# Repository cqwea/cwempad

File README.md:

This was a project i did late at night because i didnt sleep and started to design pcb's turned out it was really fun than i finished it all up there

 Bill Of Material
| Item | Quantity | Link |
| --- | --- | --- |
| Seeed XIAO RP2040 | 1 | [Link](https://www.seeedstudio.com/XIAO-RP2040-v1-0-p-5026.html) |
| MX Switches | 4 | [Link](https://www.amazon.com) |
| Keycaps | 4 | [Link](https://www.amazon.com) |
| Oled l2c 0.91inch screen | 1  | [Link](https://www.amazon.com) |
| Rotary encoder switch | 1 | [Link](https://www.amazon.com) |
| 3D Printed Case | 1 | Custom |
| Custom Pcb | 1 | Pcbway.com |

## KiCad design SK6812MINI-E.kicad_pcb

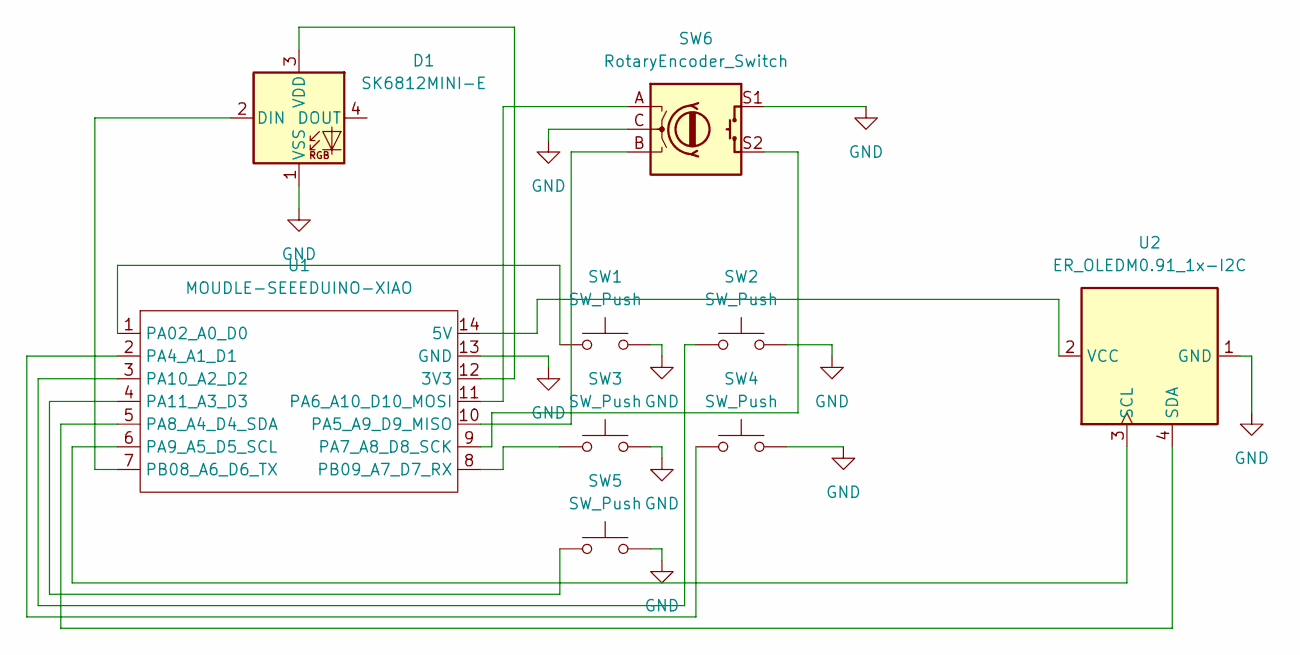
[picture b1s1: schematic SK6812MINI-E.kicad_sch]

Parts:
D1: SK6812MINI-E; LED_SK6812MINI-E_3.2x2.8mm_P1.5mm_ReverseMount
SW1, SW2, SW3, SW4, SW5: SW_Push; SW_Cherry_MX_1.00u_PCB
SW6: RotaryEncoder_Switch; RotaryEncoder_Alps_EC11E-Switch_Vertical_H20mm
U1: MOUDLE-SEEEDUINO-XIAO; XIAO-Generic-Hybrid-14P-2.54-21X17.8MM
U2: ER_OLEDM0.91_1x-I2C

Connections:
GND: D1.1 (VSS), SW1.2, SW2.2, SW3.2, SW4.2, SW5.2, SW6.C, SW6.S1, U1.13 (GND), U2.1 (GND)
unnamed: D1.2 (DIN), U1.7 (PB08_A6_D6_TX)
unnamed: D1.3 (VDD), U1.12 (3V3)
unnamed: U1.14 (5V), U2.2 (VCC)
unnamed: SW1.1, U1.1 (PA02_A0_D0)
unnamed: SW4.1, U1.2 (PA4_A1_D1)
unnamed: SW6.B, U1.10 (PA5_A9_D9_MISO)
unnamed: SW6.A, U1.11 (PA6_A10_D10_MOSI)
unnamed: SW6.S2, U1.9 (PA7_A8_D8_SCK)
unnamed: U1.5 (PA8_A4_D4_SDA), U2.4 (SDA)
unnamed: U1.6 (PA9_A5_D5_SCL), U2.3 (SCL)
unnamed: SW2.1, U1.3 (PA10_A2_D2)
unnamed: SW5.1, U1.4 (PA11_A3_D3)
unnamed: SW3.1, U1.8 (PB09_A7_D7_RX)

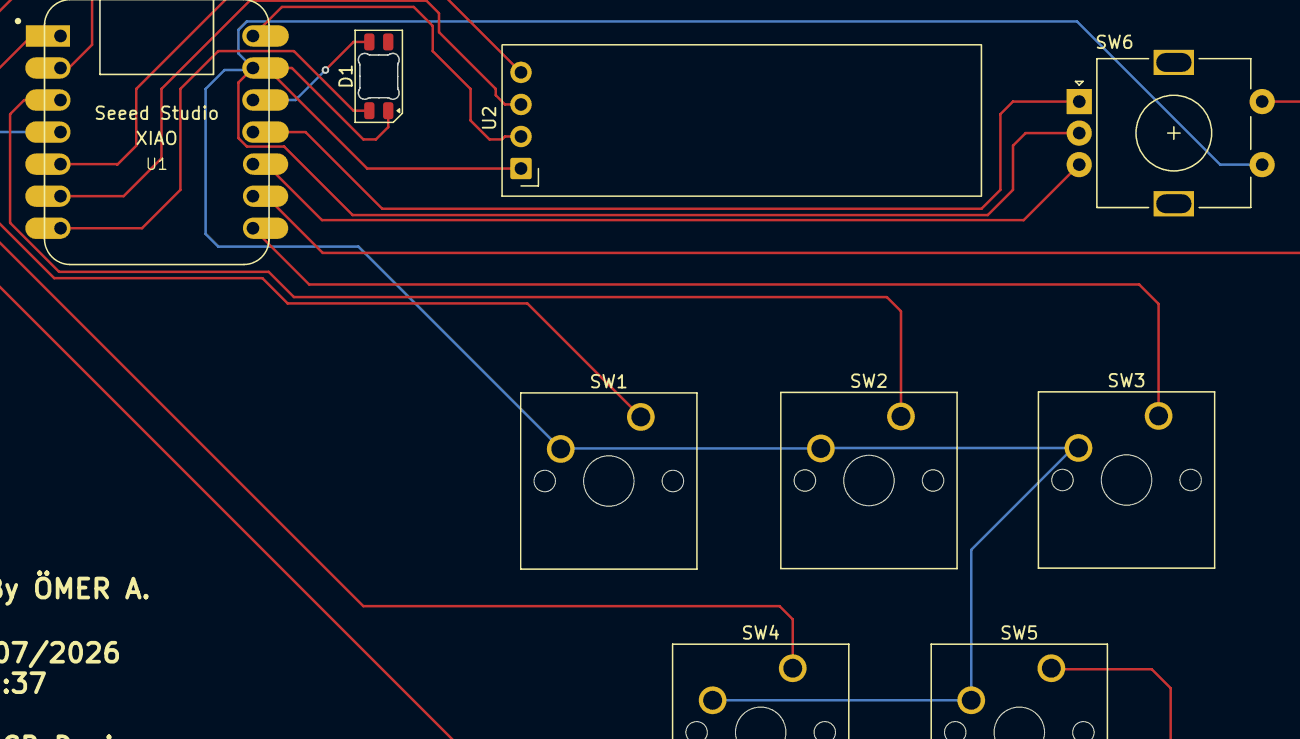
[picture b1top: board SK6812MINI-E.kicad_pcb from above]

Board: 2 copper layers, 9 parts (0 on the bottom side), 14 nets.
